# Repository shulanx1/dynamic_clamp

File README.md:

# README #

### Dynamic clamp PCB board and code ###

* Dynamic clamp circuit adapted from Desai NS, Gray R, Johnston D. A Dynamic Clamp on Every Rig. eNeuro. 2017 Oct 23;4(5):ENEURO.0250-17.2017. doi: 10.1523/ENEURO.0250-17.2017. PMID: 29085905; PMCID: PMC5659377.

### Hardware ###

* microcontroller: teensy 3.6

### Files ###

* //dynamic clamp_V1&V2: PCB designs
* //dynamic clamp_V3: PCB design for two channel dynamic clamp
* //dynamic_clamp: arduino code to upload on the microcontroller
* //processing_contrl: GUI based on processing to set parameters on the fly
* //matlab_control: matlab script to sweep the conductance for high conductance state recordings

### Contact ###

* For any questions, contact kjayant@purdue.edu.

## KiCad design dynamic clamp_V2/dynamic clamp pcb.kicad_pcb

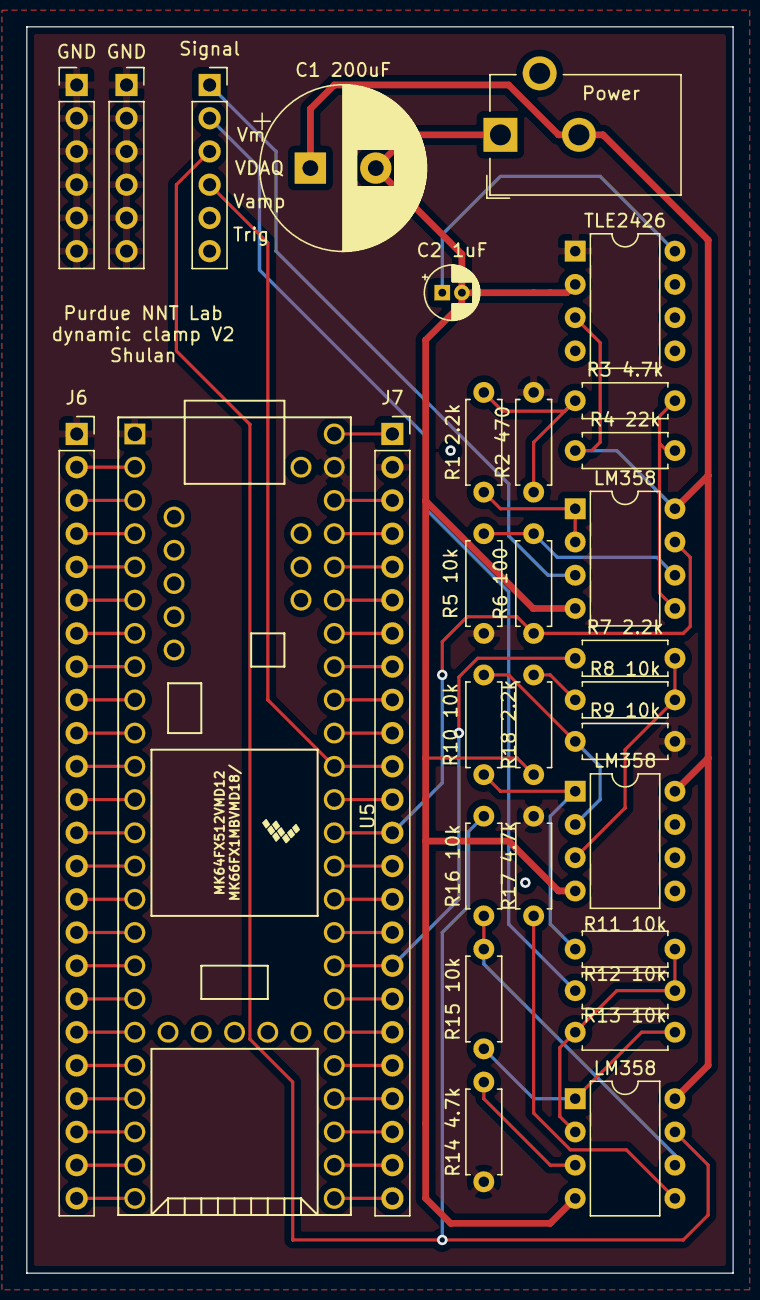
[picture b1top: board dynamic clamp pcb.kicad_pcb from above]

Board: 2 copper layers, 54.0 x 95.2 mm, 31 parts (0 on the bottom side), 66 nets.

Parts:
C1 200uF: 200uF; CP_Radial_D12.5mm_P5.00mm
C2 1uF: 1uF; CP_Radial_D4.0mm_P1.50mm
GND: Conn_01x06_Female; PinHeader_1x06_P2.54mm_Vertical
GND#2: Screw_Terminal_01x06; PinSocket_1x06_P2.54mm_Vertical
J6, J7: Conn_01x24_Female; PinSocket_1x24_P2.54mm_Vertical
LM358, LM358#2, LM358#3: LM358; DIP-8_W7.62mm
Power: Barrel_Jack_MountingPin; BarrelJack_CUI_PJ-102AH_Horizontal
R1 2.2k, R7 2.2k, R18 2.2k: 2.2k; R_Axial_DIN0207_L6.3mm_D2.5mm_P7.62mm_Horizontal
R2 470: 470; R_Axial_DIN0207_L6.3mm_D2.5mm_P7.62mm_Horizontal
R3 4.7k, R14 4.7k: 4.7k; R_Axial_DIN0207_L6.3mm_D2.5mm_P7.62mm_Horizontal
R4 22k: 22k; R_Axial_DIN0207_L6.3mm_D2.5mm_P7.62mm_Horizontal
R5 10k, R6 100, R8 10k, R9 10k, R10 10k, R11 10k, R12 10k, R13 10k, R15 10k, R16 10k: 10k; R_Axial_DIN0207_L6.3mm_D2.5mm_P7.62mm_Horizontal
R17 4.7k: 0k; R_Axial_DIN0207_L6.3mm_D2.5mm_P7.62mm_Horizontal
Signal: Screw_Terminal_01x06; PinSocket_1x06_P2.54mm_Vertical
TLE2426: TLE2426xD; DIP-8_W7.62mm
U5: Teensy3.6; Teensy35_36

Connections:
0: GND.1, GND.2, GND.3, GND.4, GND.5, GND.6, GND#2.1, GND#2.2, GND#2.3, GND#2.4, GND#2.5, GND#2.6, J6.1, J7.2, R2 470.2, R5 10k.2, R9 10k.2, R14 4.7k.1, R17 4.7k.1, TLE2426.1, U5.1, U5.52
+9V: C1 200uF.1, LM358.8, LM358#2.8, LM358#3.8, Power.2, R4 22k.1, TLE2426.3
-9V: C1 200uF.2, C2 1uF.2, LM358.4, LM358#2.4, LM358#3.4, Power.1, R18 2.2k.2, TLE2426.2
unnamed: C2 1uF.1, TLE2426.8
unnamed: LM358.3, Signal.1
unnamed: R12 10k.2, Signal.2
unnamed: LM358#3.7, R16 10k.2, Signal.3
unnamed: J7.11, Signal.4, U5.43
unnamed: J6.2, U5.2
unnamed: J6.3, U5.3
unnamed: J6.4, U5.4
unnamed: J6.5, U5.5
unnamed: J6.6, U5.6
unnamed: J6.7, U5.7
unnamed: J6.8, U5.8
unnamed: J6.9, U5.9
unnamed: J6.10, U5.10
unnamed: J6.11, U5.11
unnamed: J6.12, U5.12
unnamed: J6.13, U5.13
unnamed: J6.14, U5.14
unnamed: J6.15, U5.15
unnamed: J6.16, U5.16
unnamed: J6.17, U5.17
unnamed: J6.18, U5.18
unnamed: J6.19, U5.19
unnamed: J6.20, U5.20
unnamed: J6.21, U5.21
unnamed: J6.22, U5.22
unnamed: J6.23, U5.23
unnamed: J6.24, U5.24
unnamed: J7.1, U5.53
unnamed: J7.3, U5.51
unnamed: J7.4, U5.50
unnamed: J7.5, U5.49
unnamed: J7.6, U5.48
unnamed: J7.7, U5.47
unnamed: J7.8, U5.46
unnamed: J7.9, U5.45
unnamed: J7.10, U5.44
unnamed: J7.12, U5.42
unnamed: J7.13, LM358.7, R6 100.2, U5.41
unnamed: J7.14, U5.40
unnamed: J7.15, U5.39
unnamed: J7.16, U5.38
unnamed: J7.17, R7 2.2k.1, U5.37
unnamed: J7.18, U5.36
unnamed: J7.19, U5.35
unnamed: J7.20, U5.34
unnamed: J7.21, U5.33
unnamed: J7.22, U5.32
unnamed: J7.23, U5.31
unnamed: J7.24, U5.30
unnamed: LM358.1, LM358.2, R1 2.2k.1
unnamed: R1 2.2k.2, R2 470.1, R3 4.7k.1
unnamed: LM358.5, R3 4.7k.2, R4 22k.2
unnamed: LM358.6, R5 10k.1, R6 100.1
unnamed: LM358#2.3, R7 2.2k.2, R8 10k.2
unnamed: LM358#2.2, R9 10k.1, R10 10k.1
unnamed: LM358#2.1, R10 10k.2, R11 10k.1
unnamed: LM358#3.2, R11 10k.2, R12 10k.1, R13 10k.1
unnamed: LM358#3.1, R13 10k.2, R15 10k.1
unnamed: LM358#3.3, R14 4.7k.2
unnamed: LM358#3.6, R15 10k.2, R16 10k.1
unnamed: LM358#3.5, R17 4.7k.2
unnamed: R8 10k.1, R18 2.2k.1

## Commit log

2023-04-27 Initial Bitbucket Pipelines configuration
2023-04-27 master
2023-06-09 VGCCs added
2023-08-11 two channels
2024-03-24 minor changes
